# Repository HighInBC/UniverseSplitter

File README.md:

# UniverseSplitter
Sorts the multiverse into two equal groups.

Fuse settings on ATMEGA328P-AU: Clock Internal 8Mhz

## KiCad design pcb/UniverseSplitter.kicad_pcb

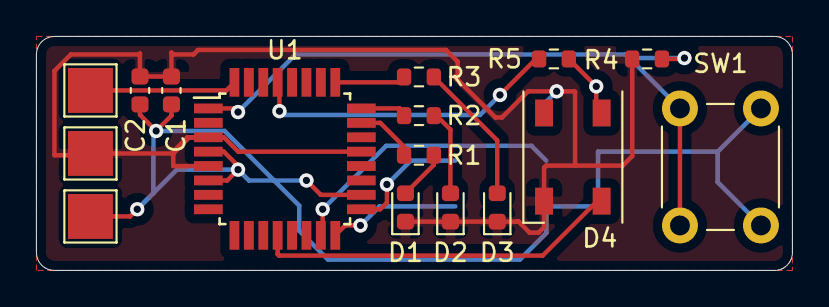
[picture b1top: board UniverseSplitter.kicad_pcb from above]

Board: 2 copper layers, 42.0 x 13.0 mm, 17 parts (1 on the bottom side), 15 nets.

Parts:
C1: 10uF; C_0603_1608Metric
C2: 100nF; C_0603_1608Metric
D1, D2, D3: LED_Small; LED_0603_1608Metric
D4: WS2812B; LED_WS2812B_PLCC4_5.0x5.0mm_P3.2mm
J2: AVR-ISP-6; PinHeader_2x03_P2.54mm_Vertical_SMD
R1, R2, R3: 200R; R_0603_1608Metric
R4, R5: 10K; R_0603_1608Metric
SW1: SW_Push; SW_PUSH_6mm
TP1: VCC; TestPoint_Pad_2.5x2.5mm
TP2: GND; TestPoint_Pad_2.5x2.5mm
TP3: Signal; TestPoint_Pad_2.5x2.5mm
U1: ATmega328P-AU; TQFP-32_7x7mm_P0.8mm

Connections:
GND: C1.2, C2.2, D1.1, D2.1, D3.1, D4.3, J2.6, R4.2, TP2.1, U1.3, U1.5, U1.21
MISO: J2.1, U1.16
MOSI: J2.4, U1.15
unnamed: D1.2, R1.1
unnamed: D2.2, R2.1
unnamed: D3.2, R3.1
unnamed: D4.4, U1.12
unnamed: R1.2, U1.23
unnamed: R2.2, U1.24
unnamed: R3.2, U1.25
unnamed: R4.1, SW1.1, U1.1
RESET: J2.5, R5.1, U1.29
SCK: J2.3, U1.17
Signal: TP3.1, U1.32
VCC: C1.1, C2.1, D4.1, J2.2, R5.2, SW1.2, TP1.1, U1.4, U1.6, U1.18

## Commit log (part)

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2024-04-20 Initial start on firmware
2024-04-20 Important fuse setting
2024-05-03 dding board files
2024-05-03 Images of schematic and 3d render
2024-05-03 This should not be a pullup, there is a hardware pulldown
